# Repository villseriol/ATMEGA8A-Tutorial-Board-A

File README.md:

# ATMEGA8A Tutorial Board A

| Revision | Description                                                                                                                                                                                                                                                                                                |
| -------- | ---------------------------------------------------------------------------------------------------------------------------------------------------------------------------------------------------------------------------------------------------------------------------------------------------------- |
| 1.0      | <ul><li>Completed initial design of evaluation board.</li></ul>                                                                                                                                                                                                                                            |
| 1.1      | <ul><li>Added series resistor to external reset for MCU.</li><li>Added series resistor to potentiometer for short-circuit protection.</li><li>Added series resistor to NE555 output for short-circuit protection.</li><li>Updated ISP-10 footprint to ISP-6.</li><li>Updated resistor footprint.</li></ul> |
| 1.2      | <ul><li>Added company logo to top silkscreen.</li><li>Changed vertical DIP switch to horizontal.</li></ul>                                                                                                                                                                                                 |

## Getting Started

### Prerequisites

```bash
# install build tools
sudo apt-get install binutils gcc-avr avr-libc uisp avrdude flex byacc bison
```

### Building

Execute the following commands in the `software-design` folder,

#### USBasp

```bash
# Windows 10
cmake --preset default
cmake --build . --preset default
# Ubuntu
cmake --preset default
cmake --build --preset default
```

#### AVRISP MKII

```bash
# Windows 10
cmake --preset avrispii
cmake --build . --preset avrispii
# Ubuntu
cmake --preset avrispii
cmake --build --preset avrispii
```

### Targets

After building the `default` preset the following targets will be made available in the generated makefile,

```bash
# flash command for a simple blink program
make flash-blink-sync
make disassemble-blink-sync

# enables the use of an external 16MHz clock source
make fuse
```

## Modules

### 7 Segment

| Diagram                                                         | Description                                                                                                                                                                                                                                                                                                                                                                    |
| --------------------------------------------------------------- | ------------------------------------------------------------------------------------------------------------------------------------------------------------------------------------------------------------------------------------------------------------------------------------------------------------------------------------------------------------------------------ |
|  | <ul><li>The 7-segment display uses all of Port D for setting the individual segments</li><li>The lower nibble of Port C is used to multiplex the currently active digit</li><li>The digits are numbered from left to right when the decimal point is positioned correctly relative to the users point of view</li><li>All segments and selection pins are active low</li></ul> |

| Microcontroller | D0  | D1  | D2  | D3  | D4  | D6  | D7  | C0      | C1      | C2      | C3      |
| --------------- | --- | --- | --- | --- | --- | --- | --- | ------- | ------- | ------- | ------- |
| 7-segment       | F   | C   | A   | G   | B   | E   | DEC | Digit 1 | Digit 2 | Digit 3 | Digit 4 |

| Value | D7  | D6  | D5  | D4  | D3  | D2  | D1  | D0  | HEX  |
| ----- | --- | --- | --- | --- | --- | --- | --- | --- | ---- |
| 0     | 1   | 0   | 0   | 0   | 1   | 0   | 0   | 0   | 0x88 |
| 1     | 1   | 1   | 1   | 0   | 1   | 1   | 0   | 1   | 0xED |
| 2     | 1   | 0   | 0   | 0   | 0   | 0   | 1   | 1   | 0x83 |
| 3     | 1   | 1   | 0   | 0   | 0   | 0   | 0   | 1   | 0xC1 |
| 4     | 1   | 1   | 1   | 1   | 0   | 1   | 0   | 0   | 0xE4 |
| 5     | 1   | 1   | 0   | 1   | 1   | 0   | 0   | 0   | 0xD0 |
| 6     | 1   | 0   | 0   | 1   | 1   | 0   | 0   | 0   | 0x90 |
| 7     | 1   | 1   | 1   | 0   | 1   | 0   | 0   | 1   | 0xE9 |
| 8     | 1   | 0   | 0   | 0   | 0   | 0   | 0   | 0   | 0x80 |
| 9     | 1   | 1   | 1   | 0   | 0   | 0   | 0   | 0   | 0xE0 |

### LED

Two active high LEDs located on pins B1 and B2 of the microcontroller.

### Potentiometer

A 50k linear potentiometer connected to pin C4. The potentiometer has two 1K resistors in series for current limiting & protection. It is expected that the analog readout on the potentiometer will never reach GND or VCC (but will come close).

### Timer

The NE555 chip feeds into the input capture pin (B0) of the microcontroller. The output frequency ranges from 100Hz~1000Hz by setting the individual DIP switches.

## Specifications

### Rev 1.0

| Top                                     | Bottom                                        |
| --------------------------------------- | --------------------------------------------- |
|  |  |

### Rev 1.1

| Top                                     | Bottom                                        |
| --------------------------------------- | --------------------------------------------- |
|  |  |

### Rev 1.2

| Top                                     | Bottom                                        |
| --------------------------------------- | --------------------------------------------- |
|  |  |

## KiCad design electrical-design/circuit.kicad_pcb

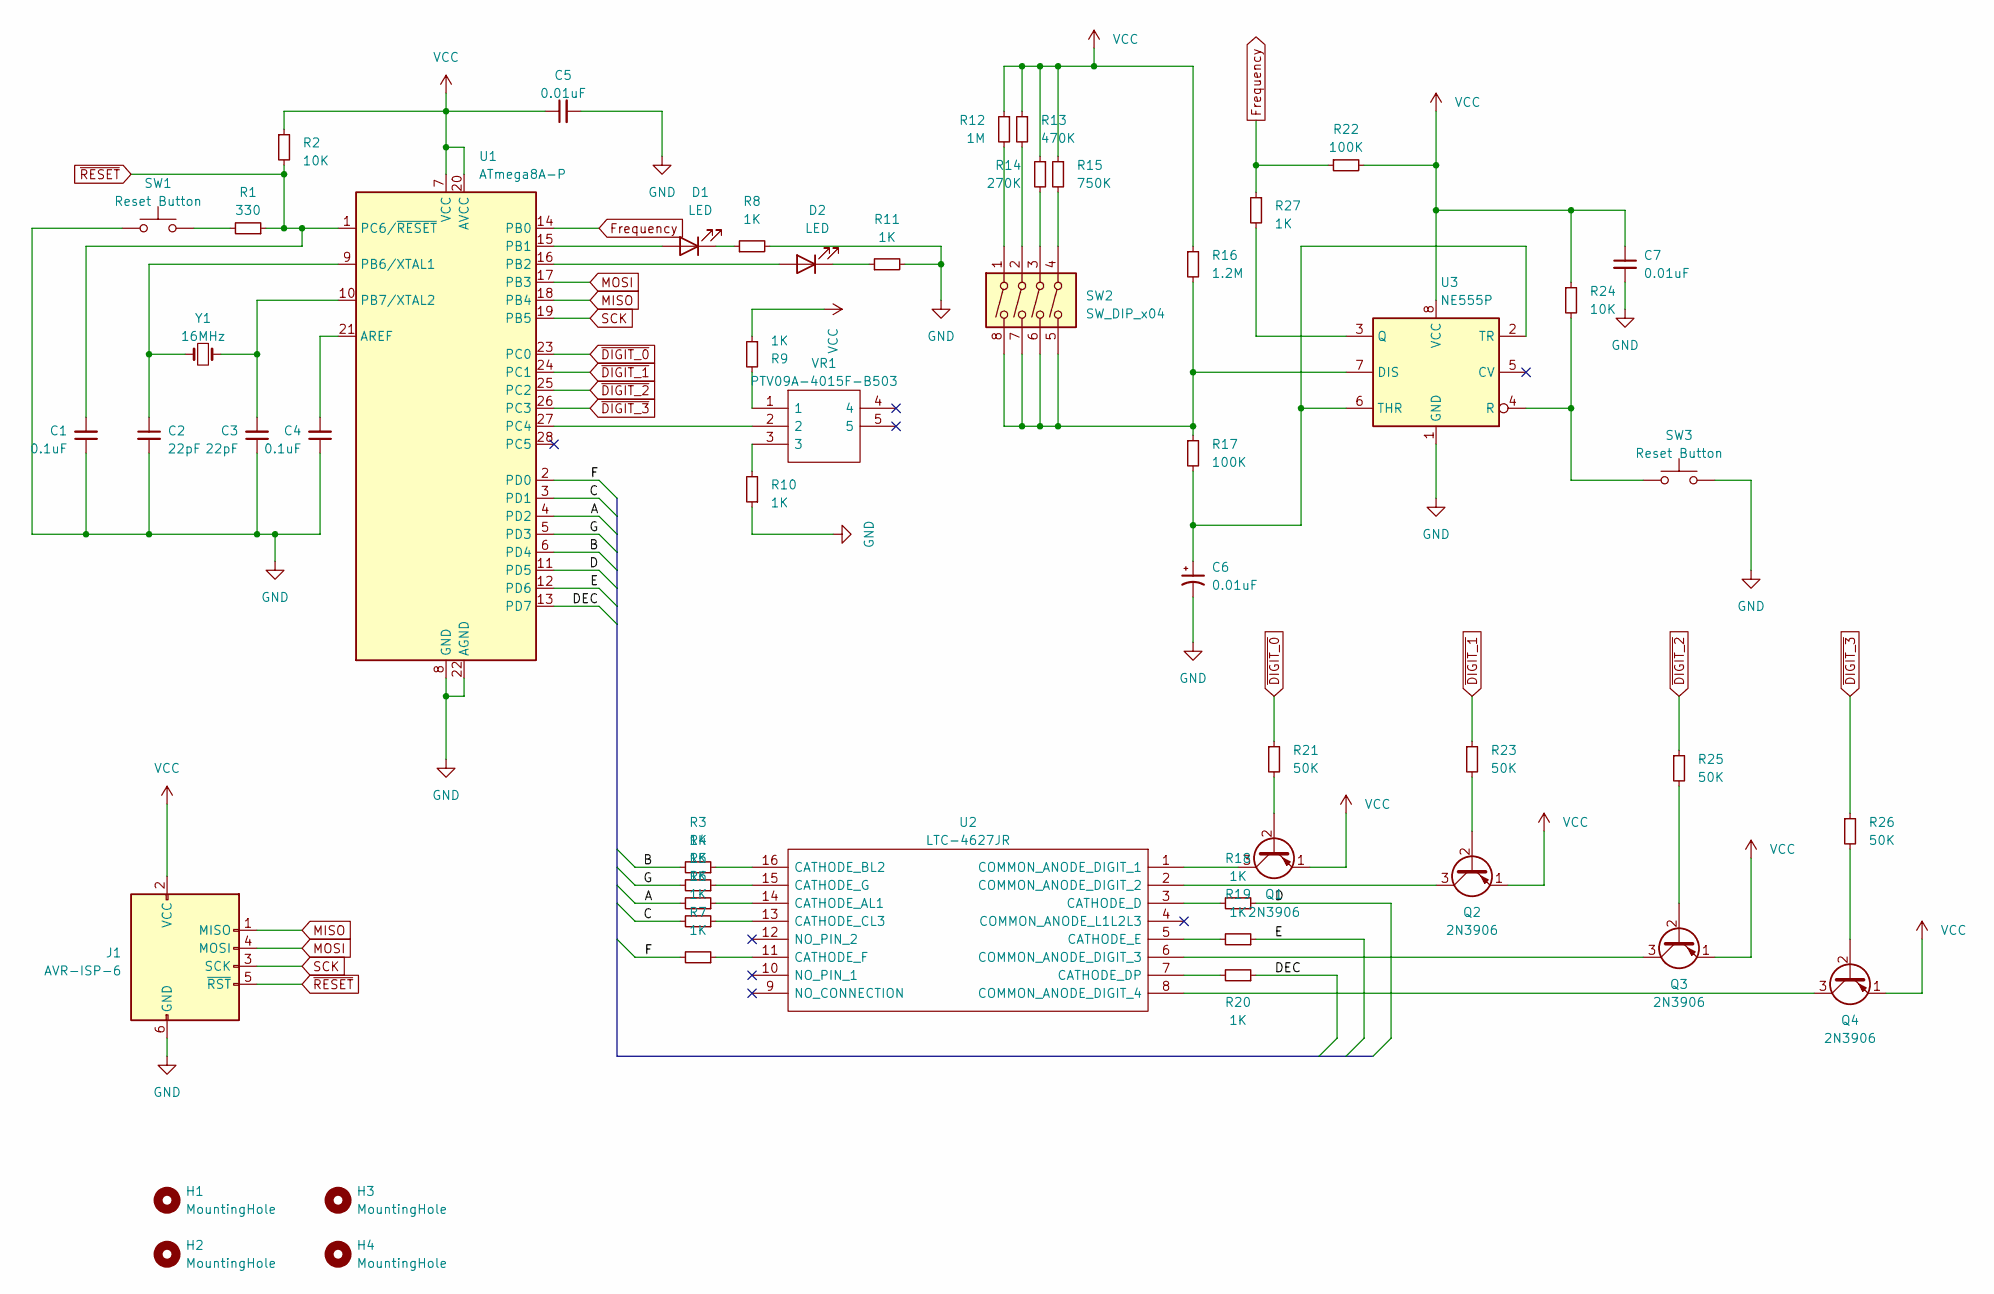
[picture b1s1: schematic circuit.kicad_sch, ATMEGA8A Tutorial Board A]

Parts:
C1, C4: 0.1uF; C_Disc_D3.0mm_W2.0mm_P2.50mm
C2, C3: 22pF; C_Disc_D3.0mm_W2.0mm_P2.50mm
C5, C6, C7: 0.01uF; C_Disc_D3.0mm_W2.0mm_P2.50mm
D1, D2: LED; LED_D3.0mm
H1, H2, H3, H4: MountingHole; MountingHole_2.2mm_M2_DIN965_Pad_TopBottom
J1: AVR-ISP-6; PinHeader_2x03_P2.54mm_Vertical
Q1, Q2, Q3, Q4: 2N3906; TO-92_Inline
R1: 330; R_Axial_DIN0207_L6.3mm_D2.5mm_P7.62mm_Horizontal
R2, R24: 10K; R_Axial_DIN0207_L6.3mm_D2.5mm_P7.62mm_Horizontal
R3, R4, R5, R6, R7, R8, R9, R10, R11, R18, R19, R20, R27: 1K; R_Axial_DIN0207_L6.3mm_D2.5mm_P7.62mm_Horizontal
R12: 1M; R_Axial_DIN0207_L6.3mm_D2.5mm_P7.62mm_Horizontal
R13: 470K; R_Axial_DIN0207_L6.3mm_D2.5mm_P7.62mm_Horizontal
R14: 270K; R_Axial_DIN0207_L6.3mm_D2.5mm_P7.62mm_Horizontal
R15: 750K; R_Axial_DIN0207_L6.3mm_D2.5mm_P7.62mm_Horizontal
R16: 1.2M; R_Axial_DIN0207_L6.3mm_D2.5mm_P7.62mm_Horizontal
R17, R22: 100K; R_Axial_DIN0207_L6.3mm_D2.5mm_P7.62mm_Horizontal
R21, R23, R25, R26: 50K; R_Axial_DIN0207_L6.3mm_D2.5mm_P7.62mm_Horizontal
SW1: Reset Button; SW_PUSH_6mm
SW2: SW_DIP_x04; SW_DIP_SPSTx04_Slide_9.78x12.34mm_W7.62mm_P2.54mm
SW3: Reset Button; SW_PUSH_6mm_H5mm
U1: ATmega8A-P; DIP-28_W7.62mm_Socket
U2: LTC-4627JR; DIPS1016W50P254L4018H725Q16N; Mouser Part Number 859-LTC-4627JR
U3: NE555P; DIP-8_W7.62mm_Socket
VR1: PTV09A-4015F-B503; PTV09A4020FB103; Mouser Part Number 652-PTV09A-4015FB503
Y1: 16MHz; Crystal_HC49-4H_Vertical

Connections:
/A: R5.2, U1.4 (PD2)
/B: R3.2, U1.6 (PD4)
/C: R6.2, U1.3 (PD1)
/D: R18.1, U1.11 (PD5)
/DEC: R20.1, U1.13 (PD7)
/E: R19.1, U1.12 (PD6)
/F: R7.2, U1.2 (PD0)
/G: R4.2, U1.5 (PD3)
Frequency: R22.1, R27.1, U1.14 (PB0)
GND: C1.1, C2.2, C3.1, C4.1, C5.2, C6.2, C7.2, J1.6 (GND), R8.2, R10.1, R11.2, SW1.1, SW3.2, U1.8 (GND), U1.22 (AGND), U3.1 (GND)
MISO: J1.1 (MISO), U1.18 (PB4)
MOSI: J1.4 (MOSI), U1.17 (PB3)
unnamed: D1.2 (A), U1.15 (PB1)
unnamed: D1.1 (K), R8.1
unnamed: D2.2 (A), U1.16 (PB2)
unnamed: D2.1 (K), R11.1
unnamed: Q1.2 (B), R21.2
unnamed: Q1.3 (C), U2.1 (COMMON_ANODE_DIGIT_1)
unnamed: Q2.2 (B), R23.2
unnamed: Q2.3 (C), U2.2 (COMMON_ANODE_DIGIT_2)
unnamed: Q3.2 (B), R25.2
unnamed: Q3.3 (C), U2.6 (COMMON_ANODE_DIGIT_3)
unnamed: Q4.2 (B), R26.2
unnamed: Q4.3 (C), U2.8 (COMMON_ANODE_DIGIT_4)
unnamed: R1.2, SW1.2
unnamed: R9.2, VR1.1
unnamed: R10.2, VR1.3
unnamed: R12.2, SW2.1
unnamed: R13.2, SW2.2
unnamed: R14.2, SW2.3
unnamed: R15.2, SW2.4
unnamed: C4.2, U1.21 (AREF)
unnamed: C2.1, U1.9 (PB6/XTAL1), Y1.2
unnamed: C3.2, U1.10 (PB7/XTAL2), Y1.1
unnamed: U1.27 (PC4), VR1.2
unnamed: R5.1, U2.14 (CATHODE_AL1)
unnamed: R3.1, U2.16 (CATHODE_BL2)
unnamed: R6.1, U2.13 (CATHODE_CL3)
unnamed: R18.2, U2.3 (CATHODE_D)
unnamed: R20.2, U2.7 (CATHODE_DP)
unnamed: R19.2, U2.5 (CATHODE_E)
unnamed: R7.1, U2.11 (CATHODE_F)
unnamed: R4.1, U2.15 (CATHODE_G)
unnamed: R16.2, R17.1, SW2.5, SW2.6, SW2.7, SW2.8, U3.7 (DIS)
unnamed: R27.2, U3.3 (Q)
unnamed: R24.2, SW3.1, U3.4 (R)
unnamed: C6.1, R17.2, U3.2 (TR), U3.6 (THR)
SCK: J1.3 (SCK), U1.19 (PB5)
VCC: C5.1, C7.1, J1.2 (VCC), Q1.1 (E), Q2.1 (E), Q3.1 (E), Q4.1 (E), R2.1, R9.1, R12.1, R13.1, R14.1, R15.1, R16.1, R22.2, R24.1, U1.7 (VCC), U1.20 (AVCC), U3.8 (VCC)
~DIGIT_0: R21.1, U1.23 (PC0)
~DIGIT_1: R23.1, U1.24 (PC1)
~DIGIT_2: R25.1, U1.25 (PC2)
~DIGIT_3: R26.1, U1.26 (PC3)
~RESET: C1.2, J1.5 (~RST), R1.1, R2.2, U1.1 (PC6/~RESET)

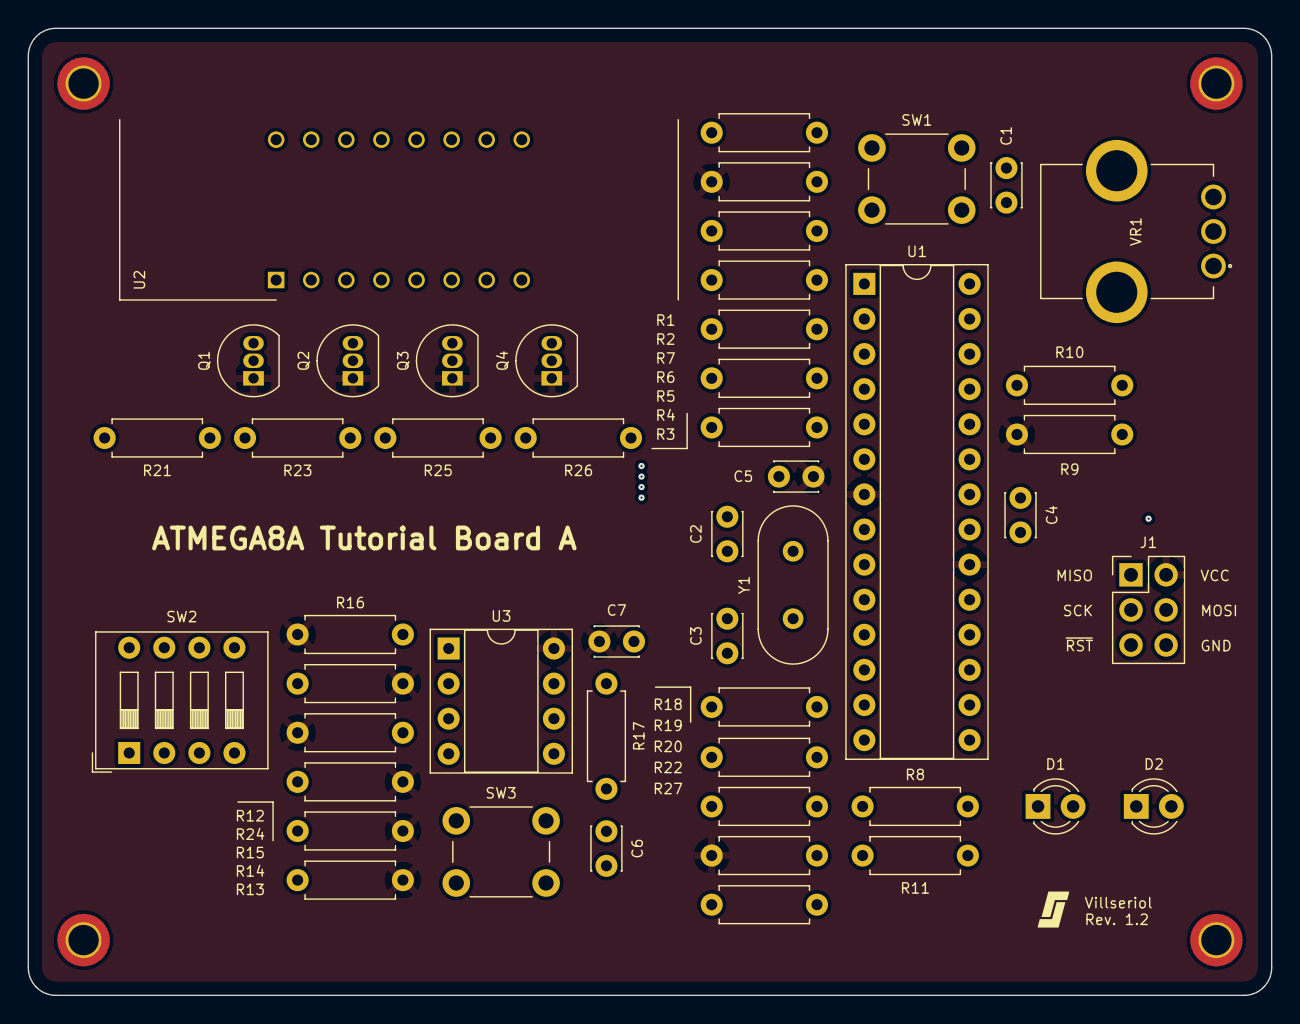
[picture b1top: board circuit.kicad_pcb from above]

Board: 4 copper layers, 90.0 x 70.0 mm, 53 parts (0 on the bottom side), 54 nets.

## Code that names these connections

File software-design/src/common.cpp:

#include "common.h"

void common::setup()
{
    __builtin_avr_cli();

    DDRD = _BV(PD0) | _BV(PD1) | _BV(PD2) | _BV(PD3) | _BV(PD4) | _BV(PD5) | _BV(PD6) | _BV(PD7);
    DDRC = _BV(PC0) | _BV(PC1) | _BV(PC2) | _BV(PC3);
    DDRB = _BV(PB1) | _BV(PB2);

    // 7-segment and led's initially off
    PORTC |= _BV(PC0) | _BV(PC1) | _BV(PC2) | _BV(PC3);
    PORTD |= _BV(PD0) | _BV(PD1) | _BV(PD2) | _BV(PD3) | _BV(PD4) | _BV(PD5) | _BV(PD6) | _BV(PD7);
    PORTB &= ~(_BV(PB1) | _BV(PB2));

    __builtin_avr_sei();
}

void common::uto7(const uint16_t value, uint8_t *buffer)
{
    uint16_t quotient = value;
    uint16_t remainder = 0;

    do
    {
        remainder = quotient % 10;
        *buffer++ = pgm_read_byte(&common::SEVEN_SEGMENT_MAP[remainder]);
        quotient /= 10;
    } while (quotient > 0);
}

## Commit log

2023-02-01 Initialized Project For Teaching 8-Bit Microcontrollers
2023-02-01 Added Include Paths For AVR Library
2023-02-01 Cmake Finally Works
2023-02-01 Added Separate Toolchain File For Cross Compilation
2023-02-05 Added Electrical Design of Evaluation Board
2023-02-05 Removing Build Directory
2023-02-05 Updating Gitignore
2023-02-06 Moving Away From Protoboard to Actual PCB Due to Production Complications
2023-02-06 Added LED's to Board
2023-02-08 Completed Initial Design of Circuit Board
2023-02-11 Added BOM
2023-02-17 Commiting Missing Files
2023-02-19 Added Production Files
2023-02-19 Removed Build Folder
2023-02-19 Separate Folder For Datasheets
2023-02-19 Added Entry For Revision 1.0
2023-02-19 Approved Evaluation Board For Production
2023-02-24 Updated Top And Bottom SVG Images
2023-02-24 Completed Design For Rev 1.0
2023-02-25 Created Parts Order List And Modified PCB Rev 1.0 Accordingly
2023-03-02 Send R1.0 to Production
2023-03-02 Added Notes For Revision 1.1
2023-03-02 Started Design For Rev 1.1
2023-03-04 Completed Build Pipeline For AVR Device
2023-03-04 Removed Comments From CMAKE File
2023-03-05 Preparing Main For Actual Code
2023-03-05 Updated Comments For Revision 1.1
2023-03-05 Changed ISP-10 Footprint to ISP-6
2023-03-05 Added Change Notes to Revision Table
2023-03-09 Updated THT Resistor Footprint
2023-03-09 Added Rev 1.1
2023-03-11 Completed Version 1.1
2023-03-11 Updated Rev1.1 Images
2023-03-13 Added Input Protection on NE555 Timer
2023-03-14 Updated Rev 1.1 Readme
2023-04-03 Got Blink Working on Circuit Board
2023-04-03 Verified Working of LCD
2023-04-04 Added Mechanical Design Folder
2023-04-04 Added Cmake Presets For Easier Building
2023-04-05 Added Simple Cofigure & Build in One Step
2023-04-05 Added Basic Startup Configuration
2023-04-05 Added Common Library
2023-04-05 Removing Build Script
2023-04-05 Added Function to Allow Multiple Entrypoints in Cmake File
2023-04-05 Changed Debug Preset to Default
2023-04-05 Updated Build Command in Readme
2023-04-05 Added Banner Comment to Common Instead of Each Entry Point
2023-04-07 Added Prettier RC File
2023-04-07 Added Floating Point And Blink ASM Examples
2023-04-07 Removing Float & Int Examples
2023-04-07 Added Windows & Ubuntu Instructions
2023-04-08 Fixed Blink Sync to Actually Work
2023-04-08 Got Library Linking Working
2023-04-08 Completed Blink Async
2023-04-08 Added Frequency Configuration to Async Blink Program
2023-04-09 Added Timing Macros
2023-04-09 Added Simple 7 Segment Code
2023-04-09 Completed 7 Segment Code
2023-04-09 Completed Simple Frequency Counter Module
2023-04-09 Added Timer Target
2023-04-09 Fixed Edge Select Issue
2023-04-10 Factored Out Some Common 7 Segment Stuff
2023-04-10 Timer Now Starts at Zero
2023-04-12 Updated Main Readme
2023-04-12 Added Some More Detailed Installation Commands
2023-04-12 Added Padding to SVG 7 Segment Image
2023-04-12 Adde White Background to SVG
2023-04-12 Adding Padding to 7 Segment Image
2023-04-12 Added Padding to P Instead of M
2023-04-12 Added 7 Segment Mapping
2023-04-12 Height Auto
2023-04-12 Added Other Modules
2023-04-12 Correctly Listed Bits For 7 Segment
2023-04-12 Correctly Listed Pins on 7 Segment
2023-04-12 Added Product Image
2023-04-12 Removed Product Image
2023-04-13 Added ADC Example Code
2023-04-13 Added Some Explaination About The Other Modules
2023-04-14 Updated Version Field in CMakePresets
2023-04-14 Completed Design of 1.2
2023-04-15 Added Info About Rev 1.2
2023-04-16 Made DIP Packages Use Socket
2023-04-26 Added Target For AVR ISP MKII
2023-05-13 Approved R1.2 For Production
2023-05-13 Added Instructions For Building With Different Programmers
